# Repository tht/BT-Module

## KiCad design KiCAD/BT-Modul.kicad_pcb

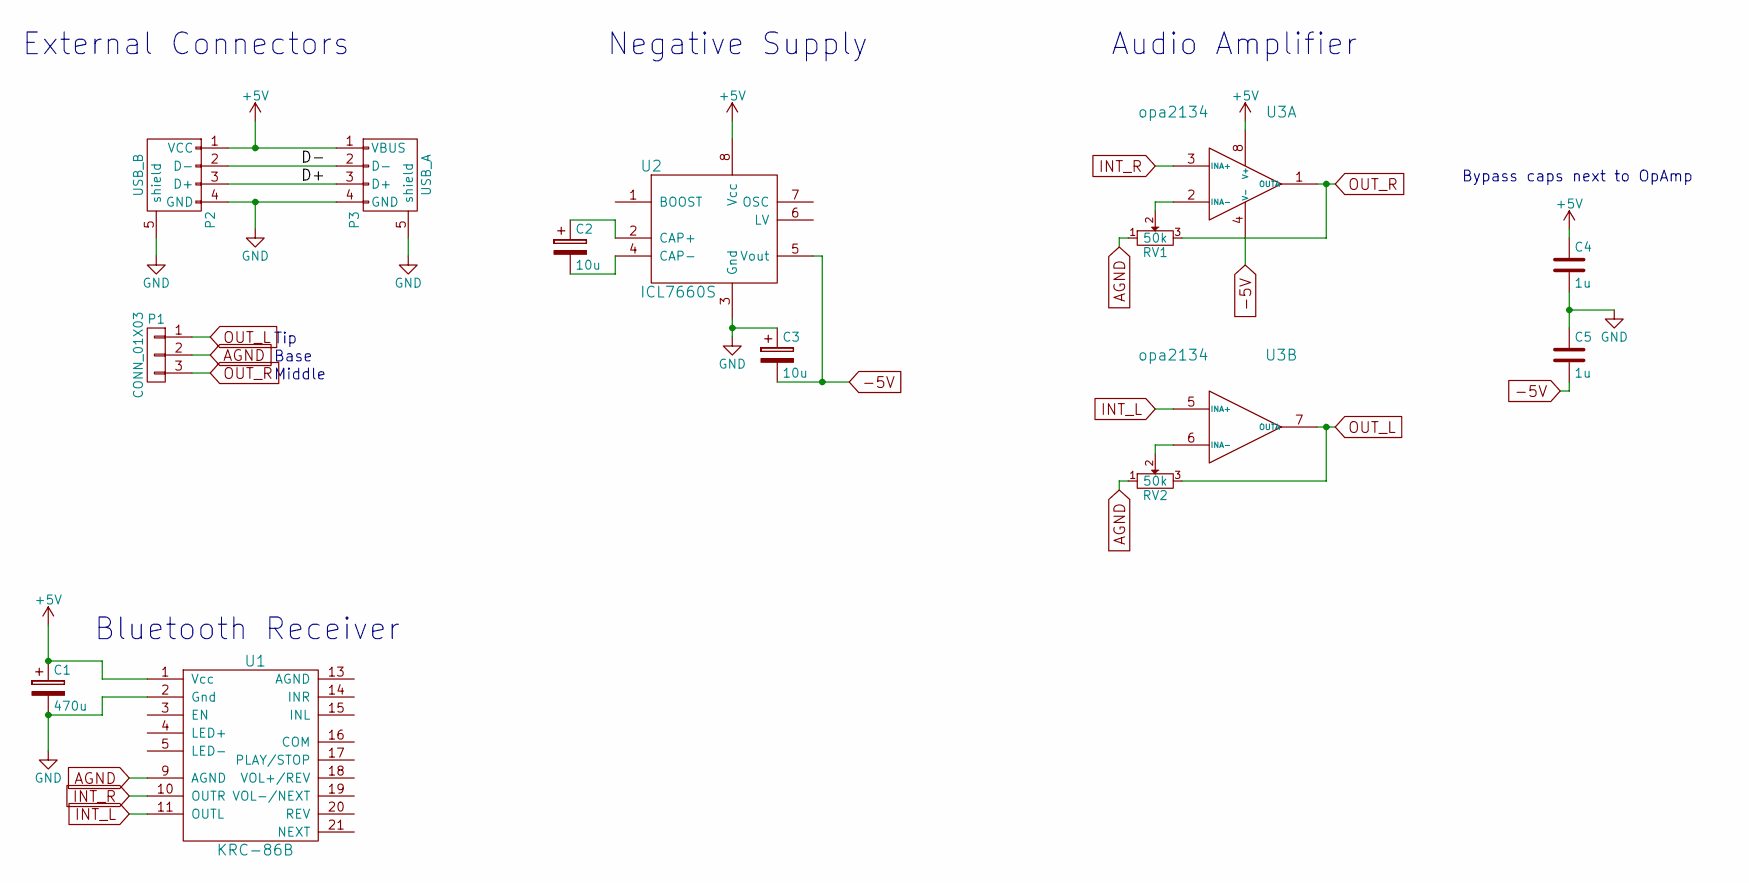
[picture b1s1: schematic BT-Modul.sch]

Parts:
C1: 470u; C_Radial_D5_L11_P2
C2, C3: 10u; C_Radial_D5_L11_P2.5
C4, C5: 1u; C_Disc_D6_P5
P1: CONN_01X03; JST_PH_B3B-PH-K_03x2.00mm_Straight
P2: USB_B; JST_PH_B5B-PH-K_05x2.00mm_Straight
P3: USB_A; USB_A_Fem_Vert
RV1, RV2: 50k; Potentiometer_Triwood_RM-065
U1: KRC-86B
U2: ICL7660S; DIP-8_W7.62mm_LongPads
U3: opa2134; DIP-8_W7.62mm_LongPads

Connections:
+5V: C1.1, C4.1, P2.1 (VCC), P3.1 (VBUS), U1.1 (Vcc), U2.8 (Vcc), U3.8 (V+)
-5V: C3.2, C5.2, U2.5 (Vout), U3.4 (V-)
/D+: P2.3 (D+), P3.3 (D+)
/D-: P2.2 (D-), P3.2 (D-)
AGND: P1.2, RV1.1, RV2.1, U1.9 (AGND)
GND: C1.2, C3.1, C4.2, C5.1, P2.4 (GND), P2.5 (shield), P3.4 (GND), P3.5 (shield), U1.2 (Gnd), U2.3 (Gnd)
INT_L: U1.11 (OUTL), U3.5 (INA+)
INT_R: U1.10 (OUTR), U3.3 (INA+)
unnamed: C2.1, U2.2 (CAP+)
unnamed: C2.2, U2.4 (CAP-)
unnamed: RV1.2, U3.2 (INA-)
unnamed: RV2.2, U3.6 (INA-)
OUT_L: P1.1, RV2.3, U3.7 (OUTA)
OUT_R: P1.3, RV1.3, U3.1 (OUTA)

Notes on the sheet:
External Connectors
Negative Supply
Bluetooth Receiver
Audio Amplifier
Tip
Middle
Base
Bypass caps next to OpAmp

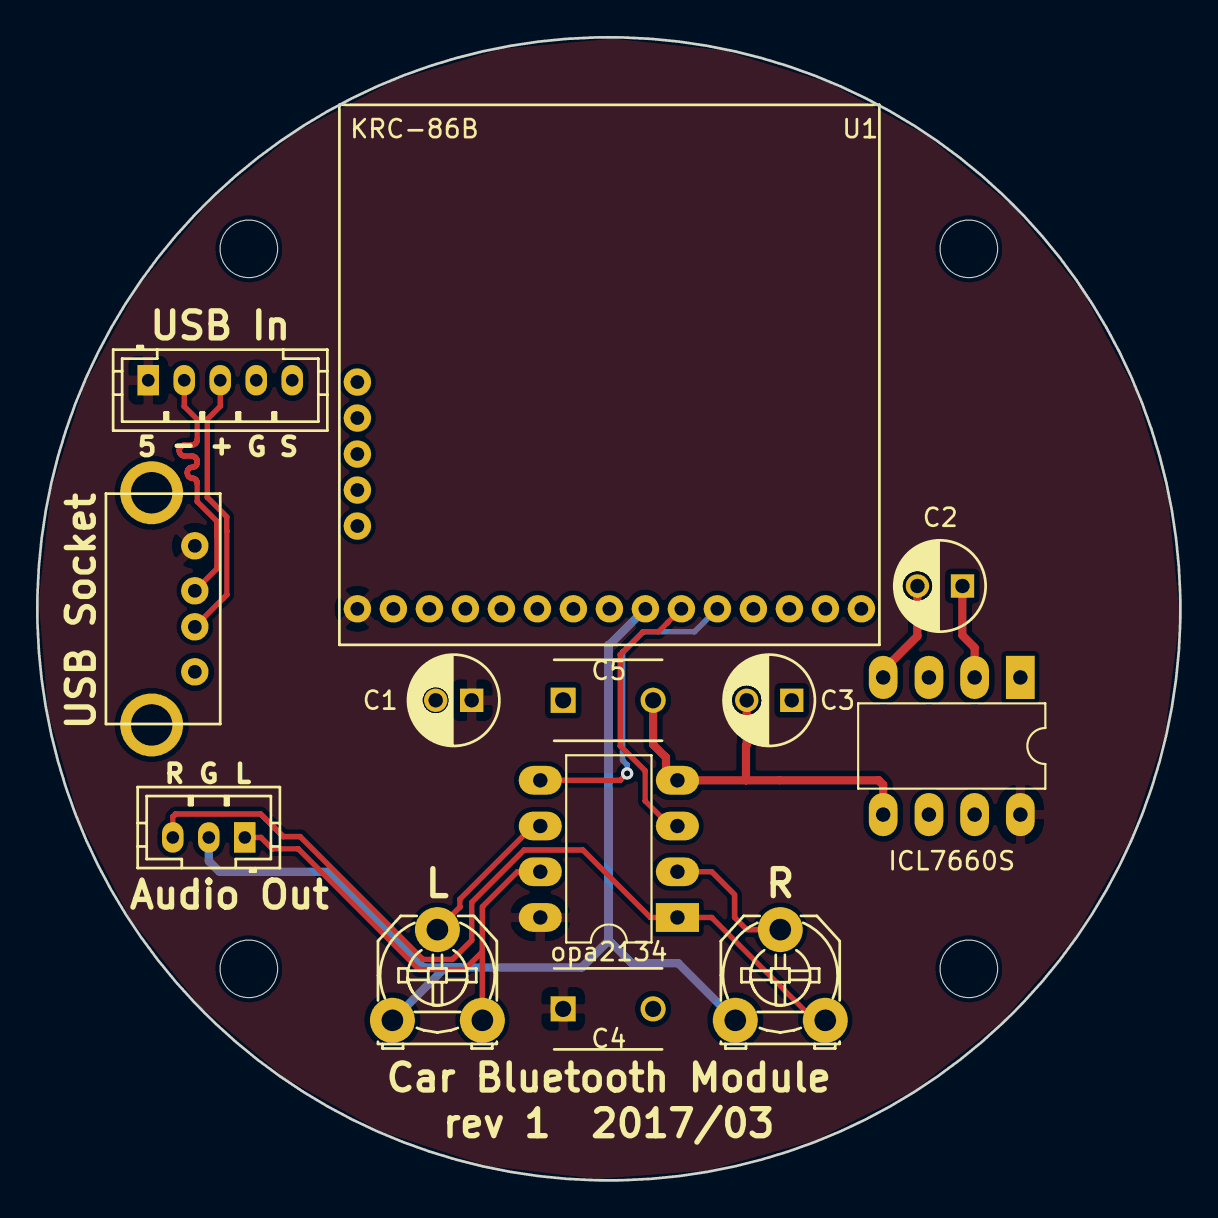
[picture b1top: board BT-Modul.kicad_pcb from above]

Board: 2 copper layers, 63.5 x 63.5 mm, 13 parts (0 on the bottom side), 14 nets.

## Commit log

2017-02-19 Added schema and an image
2017-02-19 Ready for ordering
2017-02-26 Rev 1 as ordered
